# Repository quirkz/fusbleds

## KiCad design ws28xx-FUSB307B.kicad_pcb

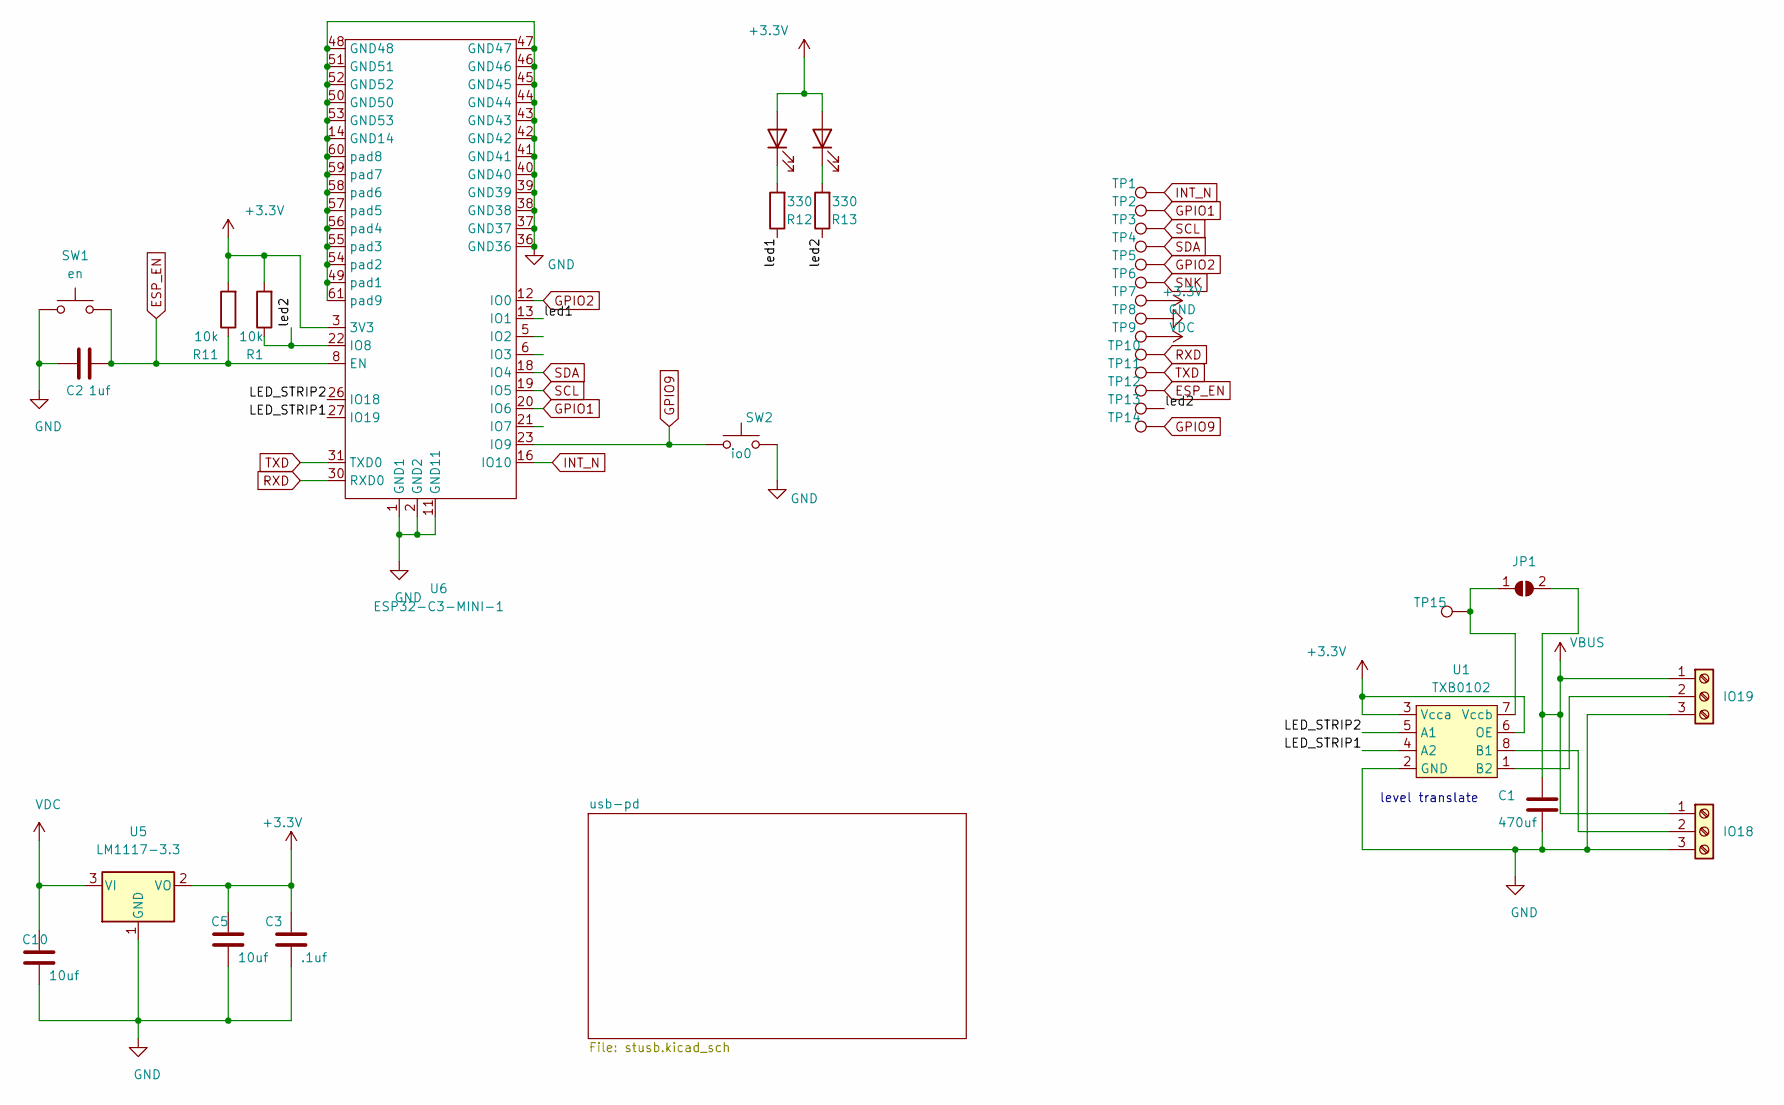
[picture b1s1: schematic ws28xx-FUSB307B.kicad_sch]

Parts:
C1: 470uf; C_Elec_10x10.2
C2: 1uf; C_0603_1608Metric
C3: .1uf; C_0603_1608Metric
C5, C10: 10uf; C_0805_2012Metric
D1, D2: LED; LED_0603_1608Metric
IO18: Screw_Terminal_01x03; TerminalBlock_Phoenix_PT-1,5-3-3.5-H_1x03_P3.50mm_Horizontal
IO19: Screw_Terminal_01x0; TerminalBlock_Phoenix_PT-1,5-3-3.5-H_1x03_P3.50mm_Horizontal
JP1: SolderJumper_2_Open; SolderJumper-2_P1.3mm_Bridged_RoundedPad1.0x1.5mm
R1, R11: 10k; R_0603_1608Metric
R12, R13: 330; R_0603_1608Metric
SW1: en; SW_Push_1P1T_NO_Vertical
SW2: io0; SW_Push_1P1T_NO_Vertical
TP1, TP2, TP3, TP4, TP5, TP6, TP7, TP8, TP9, TP10, TP11, TP12, TP13, TP14: TestPoint; TestPoint_Pad_D2.0mm
TP15: TestPoint; TestPoint_THTPad_D3.0mm_Drill1.5mm
U1: TXB0102; SOIC-8
U5: LM1117-3.3; SOT-223
U6: ESP32-C3-MINI-1

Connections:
+3V3: C3.1, C5.1, D1.2 (A), D2.2 (A), R1.2, R11.2, TP7.1, U1.3 (Vcca), U1.6 (OE), U5.2 (VO), U6.3 (3V3); also elsewhere on the board
/LED_STRIP1: U1.4 (A2), U6.27 (IO19)
/LED_STRIP2: U1.5 (A1), U6.26 (IO18)
/led1: R12.1, U6.13 (IO1)
/led2: R1.1, R13.1, TP13.1, U6.22 (IO8)
ESP_EN: C2.2, R11.1, SW1.2, TP12.1, U6.8 (EN); also elsewhere on the board
GND: C1.2, C2.1, C3.2, C5.2, C10.2, IO18.3, IO19.3, SW1.1, SW2.2, TP8.1, U1.2 (GND), U5.1 (GND), U6.1 (GND1), U6.2 (GND2), U6.11 (GND11), U6.14 (GND14), U6.36 (GND36), U6.37 (GND37), U6.38 (GND38), U6.39 (GND39), U6.40 (GND40), U6.41 (GND41), U6.42 (GND42), U6.43 (GND43), U6.44 (GND44), U6.45 (GND45), U6.46 (GND46), U6.47 (GND47), U6.48 (GND48), U6.49 (pad1), U6.50 (GND50), U6.51 (GND51), U6.52 (GND52), U6.53 (GND53), U6.54 (pad2), U6.55 (pad3), U6.56 (pad4), U6.57 (pad5), U6.58 (pad6), U6.59 (pad7), U6.60 (pad8), U6.61 (pad9); also elsewhere on the board
GPIO1: TP2.1, U6.20 (IO6); also elsewhere on the board
GPIO2: TP5.1, U6.12 (IO0); also elsewhere on the board
GPIO9: SW2.1, TP14.1, U6.23 (IO9); also elsewhere on the board
INT_N: TP1.1, U6.16 (IO10); also elsewhere on the board
unnamed: D1.1 (K), R12.2
unnamed: D2.1 (K), R13.2
unnamed: IO18.2, U1.8 (B1)
unnamed: IO19.2, U1.1 (B2)
unnamed: JP1.1 (A), TP15.1, U1.7 (Vccb)
RXD: TP10.1, U6.30 (RXD0); also elsewhere on the board
SCL: TP3.1, U6.19 (IO5); also elsewhere on the board
SDA: TP4.1, U6.18 (IO4); also elsewhere on the board
SNK: TP6.1; also elsewhere on the board
TXD: TP11.1, U6.31 (TXD0); also elsewhere on the board
VBUS: C1.1, IO18.1, IO19.1, JP1.2 (B); also elsewhere on the board
VDC: C10.1, TP9.1, U5.3 (VI); also elsewhere on the board

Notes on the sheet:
level translate

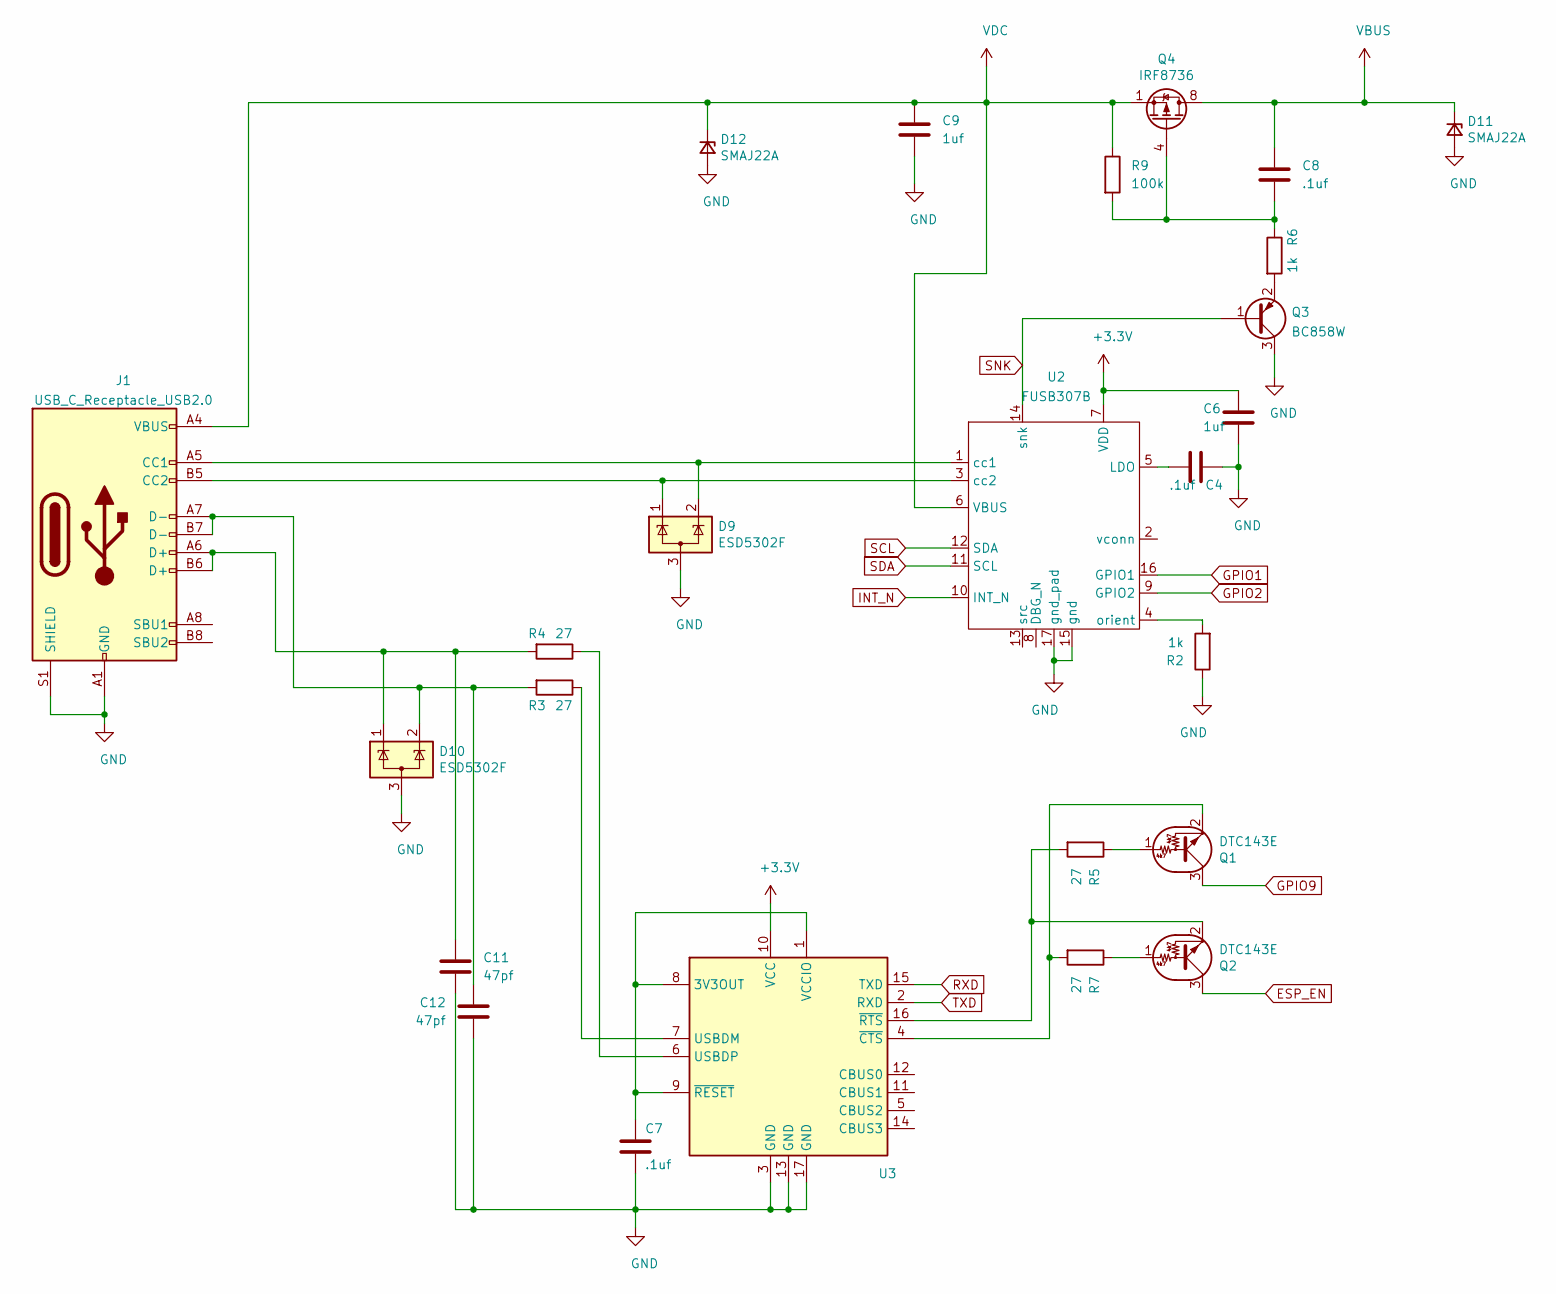
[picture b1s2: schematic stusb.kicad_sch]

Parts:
C4, C7, C8: .1uf; C_0603_1608Metric
C6, C9: 1uf; C_0603_1608Metric
C11, C12: 47pf; C_0603_1608Metric
D9, D10: ESD5302F; SOT-23
D11, D12: SMAJ22A; D_SMA
J1: USB_C_Receptacle_USB2.0; USB_C_Receptacle_Palconn_UTC16-G
Q1, Q2: DTC143E; SOT-323_SC-70
Q3: BC858W; SOT-323_SC-70
Q4: IRF8736; SOIC-8_3.9x4.9mm_P1.27mm
R2, R6: 1k; R_0603_1608Metric
R3, R4, R5, R7: 27; R_0603_1608Metric
R9: 100k; R_0603_1608Metric
U2: FUSB307B; HVQFN-16-1EP_3x3mm_P0.5mm_EP1.5x1.5mm
U3: FT230XQ; QFN-16-1EP_4x4mm_P0.65mm_EP2.1x2.1mm

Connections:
+3V3: C6.1, U2.7 (VDD), U3.10 (VCC); also elsewhere on the board
ESP_EN: Q2.3 (C); also elsewhere on the board
GND: C4.1, C6.2, C7.2, C9.2, C11.2, C12.2, D9.3 (A), D10.3 (A), D11.2 (A), D12.2 (A), J1.A1 (GND), J1.A12 (GND), J1.B1 (GND), J1.B12 (GND), J1.S1 (SHIELD), Q3.3 (C), R2.1, U2.15 (gnd), U2.17 (gnd_pad), U3.3 (GND), U3.13 (GND), U3.17 (GND); also elsewhere on the board
GPIO1: U2.16 (GPIO1); also elsewhere on the board
GPIO2: U2.9 (GPIO2); also elsewhere on the board
GPIO9: Q1.3 (C); also elsewhere on the board
INT_N: U2.10 (INT_N); also elsewhere on the board
unnamed: C4.2, U2.5 (LDO)
unnamed: C7.1, U3.1 (VCCIO), U3.8 (3V3OUT), U3.9 (~RESET)
unnamed: C8.2, Q4.4 (G), R6.1, R9.2
unnamed: C11.1, D10.1 (K), J1.A6 (D+), J1.B6 (D+), R4.2
unnamed: C12.1, D10.2 (K), J1.A7 (D-), J1.B7 (D-), R3.2
unnamed: D9.1 (K), J1.B5 (CC2), U2.3 (cc2)
unnamed: D9.2 (K), J1.A5 (CC1), U2.1 (cc1)
unnamed: Q1.1 (B), R5.1
unnamed: Q1.2 (E), R7.2, U3.4 (~CTS)
unnamed: Q2.1 (B), R7.1
unnamed: Q2.2 (E), R5.2, U3.16 (~RTS)
unnamed: Q3.2 (E), R6.2
unnamed: R2.2, U2.4 (orient)
unnamed: R3.1, U3.7 (USBDM)
unnamed: R4.1, U3.6 (USBDP)
RXD: U3.15 (TXD); also elsewhere on the board
SCL: U2.12 (SDA); also elsewhere on the board
SDA: U2.11 (SCL); also elsewhere on the board
SNK: Q3.1 (B), U2.14 (snk); also elsewhere on the board
TXD: U3.2 (RXD); also elsewhere on the board
VBUS: C8.1, D11.1 (K), Q4.5 (D), Q4.6 (D), Q4.7 (D), Q4.8 (D); also elsewhere on the board
VDC: C9.1, D12.1 (K), J1.A4 (VBUS), J1.A9 (VBUS), J1.B4 (VBUS), J1.B9 (VBUS), Q4.1 (S), Q4.2 (S), Q4.3 (S), R9.1, U2.6 (VBUS); also elsewhere on the board

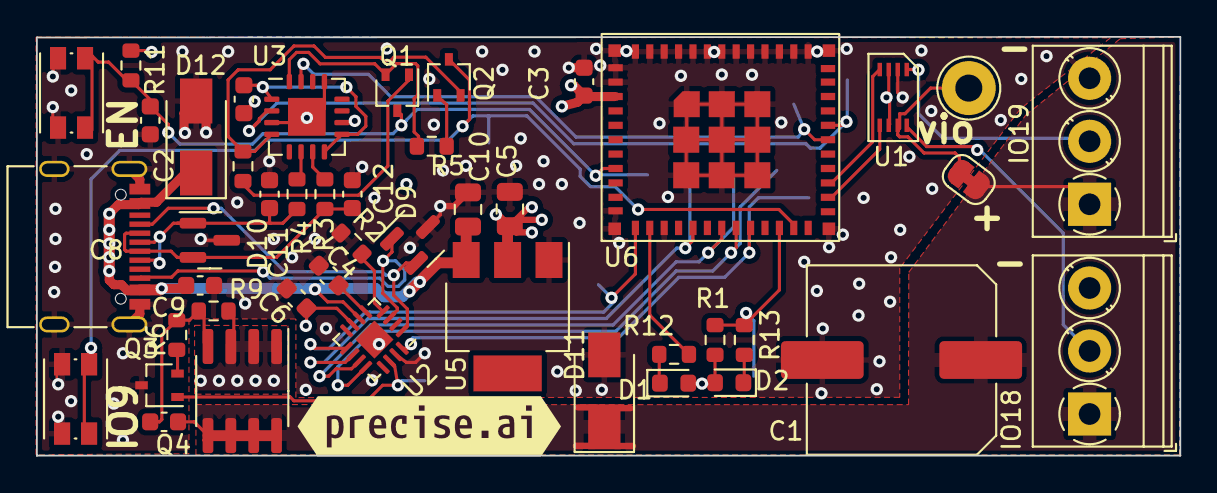
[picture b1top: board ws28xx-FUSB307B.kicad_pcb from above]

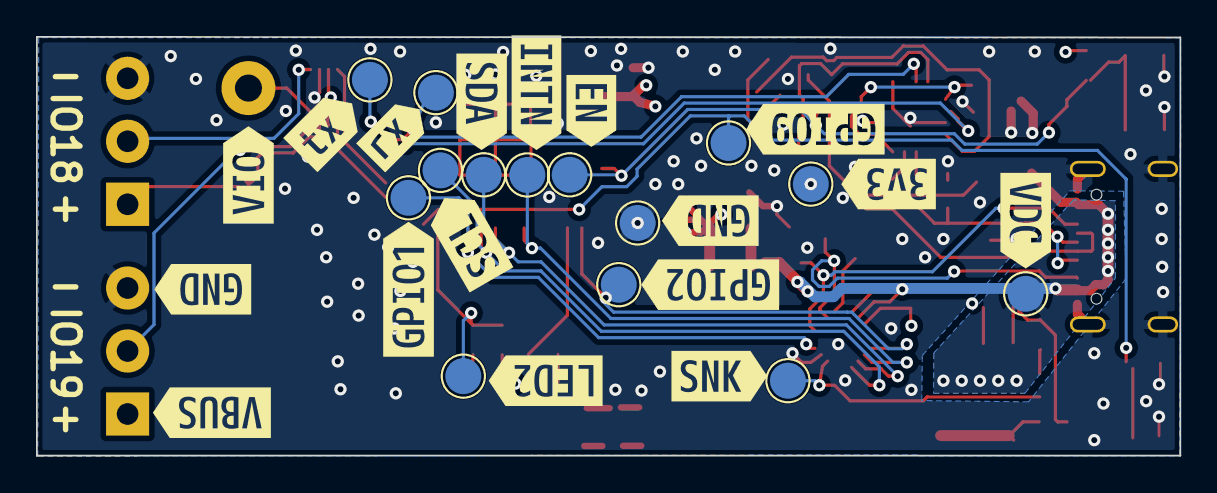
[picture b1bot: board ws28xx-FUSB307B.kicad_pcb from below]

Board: 4 copper layers, 63.5 x 23.3 mm, 77 parts (31 on the bottom side), 38 nets.

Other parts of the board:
svg2mod, svg2mod#2, svg2mod#3, svg2mod#4, svg2mod#5, svg2mod#6, svg2mod#7, svg2mod#8, svg2mod#9, svg2mod#10, svg2mod#11, svg2mod#12, svg2mod#13, svg2mod#14, svg2mod#15, svg2mod#16, svg2mod#17, svg2mod#18: G***; svg2mod

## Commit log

2021-10-11 add schematic pdf
2021-10-11 add video
2021-10-11 transistor oops
2021-10-17 drc fixes
2022-12-06 Test
